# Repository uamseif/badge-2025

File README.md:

# 🛠️ C1b3rtr4cks Badge 2025

Este repositorio contiene el diseño y firmware de la **badge oficial del evento de ciberseguridad [Cibertracks](https://www.c1b3rtr4cks.es/)**. Este badge está compuesta por **tres placas PCB** ensambladas como un **sandwich**, cada una diseñada en **KiCad**. Además de su función identificativa, su forma permite utilizarla como **portatarjetas físico** para credenciales o tarjetas del evento.

---

## 🧭 Descripción del Proyecto

- 🔧 **Diseño multicapa:** 3 placas PCB ensambladas en forma de sandwich.
- 🎨 **Diseño personalizado:** Adaptada para representar visualmente la identidad del evento.
- 💾 **Firmware en C:** Corre en un **CH32V003**, un microcontrolador RISC-V.
- 🪪 **Funcionalidad dual:** Badge electrónica + portatarjetas físico.

---

## 🧩 Hardware

La placa está diseñada en tres capas, cada una como un proyecto independiente en **KiCad**:

- **badge2025**: Capa frontal. Incluye LEDs, botones y detalles gráficos del evento.
- **middle_frame**: Elemento mecánico que actua como separador y de retenedor de tarjetas.
- **front_frame**: Capa frontal que extiende el diseño de la placa principal.

Estas capas se ensamblan de forma compacta, resultando en una badge robusta y funcional, apta para colgar con lanyard o sujetar una tarjeta del evento.

---

## 💻 Firmware

El firmware está ubicado en `software` y está desarrollado en **C** usando **PlatformIO**.

Se trata de una serie de minijuegos a los que se puede jugar con otra persona juntando dos placas. 

### 📦 Requisitos

- [PlatformIO](https://platformio.org/)
- Programador compatible con CH32V003 (ej. WCH-LinkE, USB-UART + BOOT0)

## ▶️ ¿Cómo usar la placa?

En la siguiente [página](HOW-TO-USE.md) encontramos instrucciones de como usar la placa y jugar con ella.

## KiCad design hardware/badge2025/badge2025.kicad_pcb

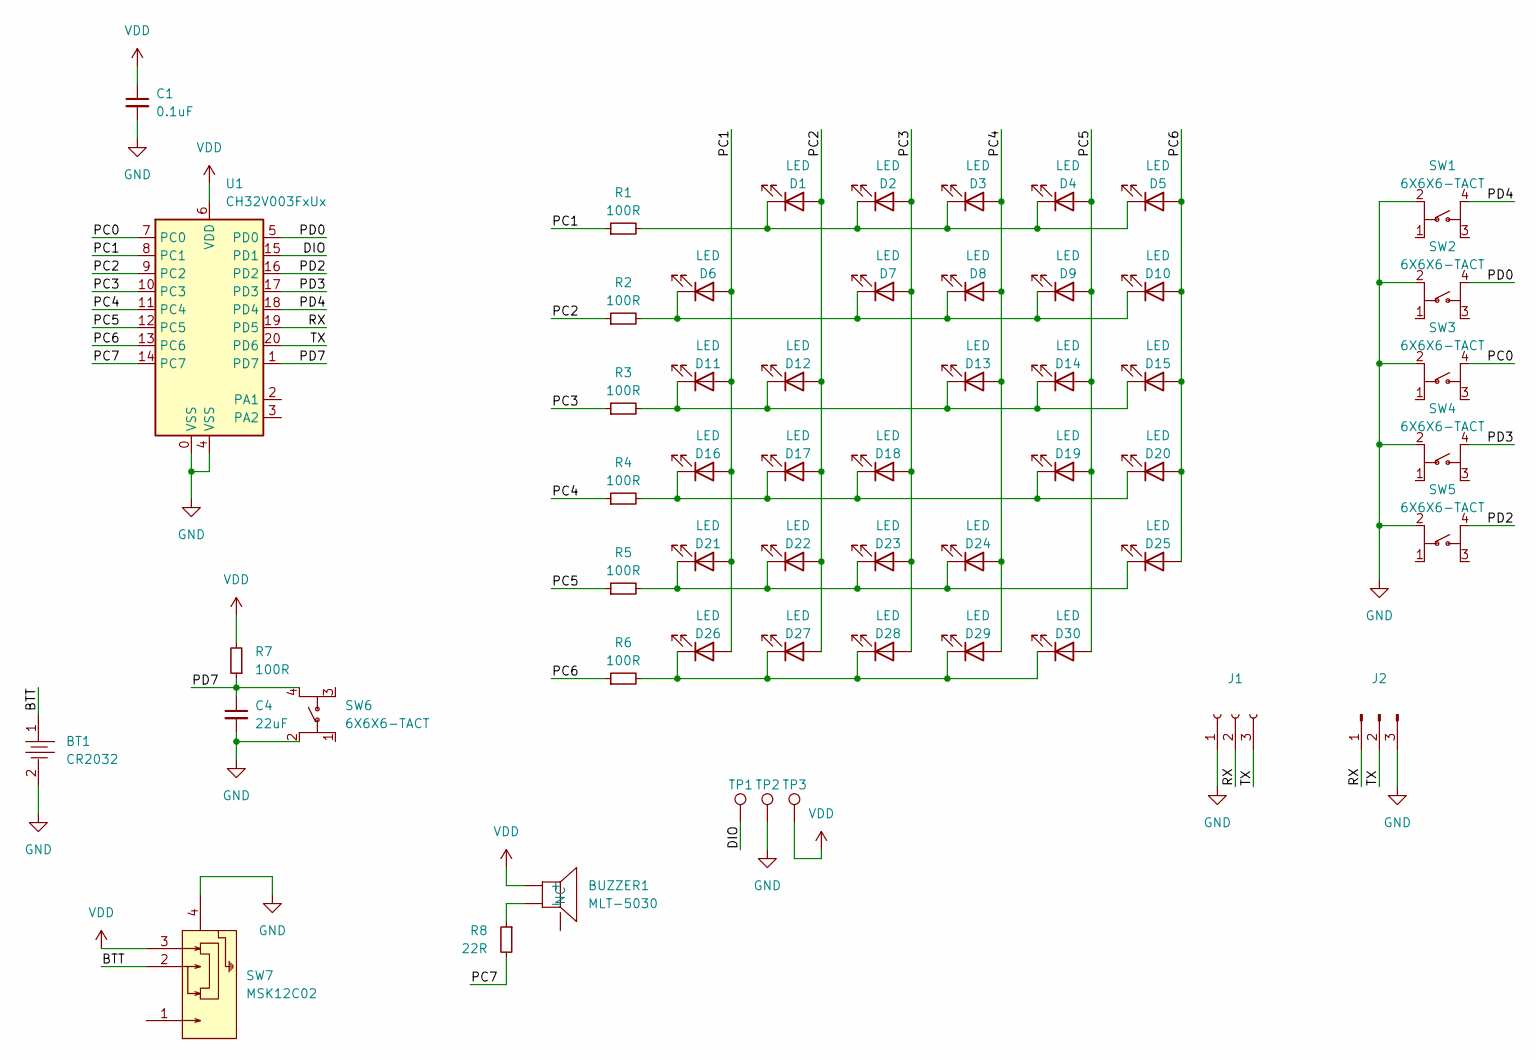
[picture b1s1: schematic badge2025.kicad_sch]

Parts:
BT1: CR2032; BAT-SMD_MY-2032-08
BUZZER1: MLT-5030; BUZ-SMD_3P-L5.2-W5.2-P3.50-BR
C1: 0.1uF; C_0805_2012Metric
C4: 22uF; C_0805_2012Metric
D1, D2, D3, D4, D5, D6, D7, D8, D9, D10, D11, D12, D13, D14, D15, D16, D17, D18, D19, D20, D21, D22, D23, D24, D25, D26, D27, D28, D29, D30: LED; LED_0805_2012Metric
J1: Conn_01x03_Socket; HDR-SMD_3P-P2.54-H-M
J2: Conn_01x03_Pin; HDR-SMD_3P-P2.54-H-F-L11.5
R1, R2, R3, R4, R5, R6, R7: 100R; R_0805_2012Metric
R8: 22R; R_0805_2012Metric
SW1, SW2, SW3, SW4, SW5, SW6: 6X6X6-TACT; SW-SMD_4P-L6.0-W6.0-P4.50-LS9.2
SW7: MSK12C02; SW-TH_MSK12C02
TP1, TP2, TP3: TestPoint; TestPoint_Pad_D1.5mm
U1: CH32V003FxUx; QFN-20-1EP_3x3mm_P0.4mm_EP1.65x1.65mm

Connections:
/BTT: BT1.1, SW7.2
/DIO: TP1.1, U1.15 (PD1)
/PC0: SW3.4 (D), U1.7 (PC0)
/PC1: D6.2 (A), D11.2 (A), D16.2 (A), D21.2 (A), D26.2 (A), R1.1, U1.8 (PC1)
/PC2: D1.2 (A), D12.2 (A), D17.2 (A), D22.2 (A), D27.2 (A), R2.1, U1.9 (PC2)
/PC3: D2.2 (A), D7.2 (A), D18.2 (A), D23.2 (A), D28.2 (A), R3.1, U1.10 (PC3)
/PC4: D3.2 (A), D8.2 (A), D13.2 (A), D24.2 (A), D29.2 (A), R4.1, U1.11 (PC4)
/PC5: D4.2 (A), D9.2 (A), D14.2 (A), D19.2 (A), D30.2 (A), R5.1, U1.12 (PC5)
/PC6: D5.2 (A), D10.2 (A), D15.2 (A), D20.2 (A), D25.2 (A), R6.1, U1.13 (PC6)
/PC7: R8.2, U1.14 (PC7)
/PD0: SW2.4 (D), U1.5 (PD0)
/PD2: SW5.4 (D), U1.16 (PD2)
/PD3: SW4.4 (D), U1.17 (PD3)
/PD4: SW1.4 (D), U1.18 (PD4)
/PD7: C4.1, R7.1, SW6.4 (D), U1.1 (PD7)
/RX: J1.2, J2.1, U1.19 (PD5)
/TX: J1.3, J2.2, U1.20 (PD6)
/XI: U1.2 (PA1)
/XO: U1.3 (PA2)
GND: BT1.2, C1.2, C4.2, J1.1, J2.3, SW1.2 (B), SW2.2 (B), SW3.2 (B), SW4.2 (B), SW5.2 (B), SW6.2 (B), SW7.4, TP2.1, U1.0 (VSS), U1.4 (VSS)
unnamed: BUZZER1.3 (-), R8.1
unnamed: D1.1 (K), D2.1 (K), D3.1 (K), D4.1 (K), D5.1 (K), R1.2
unnamed: D6.1 (K), D7.1 (K), D8.1 (K), D9.1 (K), D10.1 (K), R2.2
unnamed: D11.1 (K), D12.1 (K), D13.1 (K), D14.1 (K), D15.1 (K), R3.2
unnamed: D16.1 (K), D17.1 (K), D18.1 (K), D19.1 (K), D20.1 (K), R4.2
unnamed: D21.1 (K), D22.1 (K), D23.1 (K), D24.1 (K), D25.1 (K), R5.2
unnamed: D26.1 (K), D27.1 (K), D28.1 (K), D29.1 (K), D30.1 (K), R6.2
VDD: BUZZER1.2 (+), C1.1, R7.2, SW7.3, TP3.1, U1.6 (VDD)

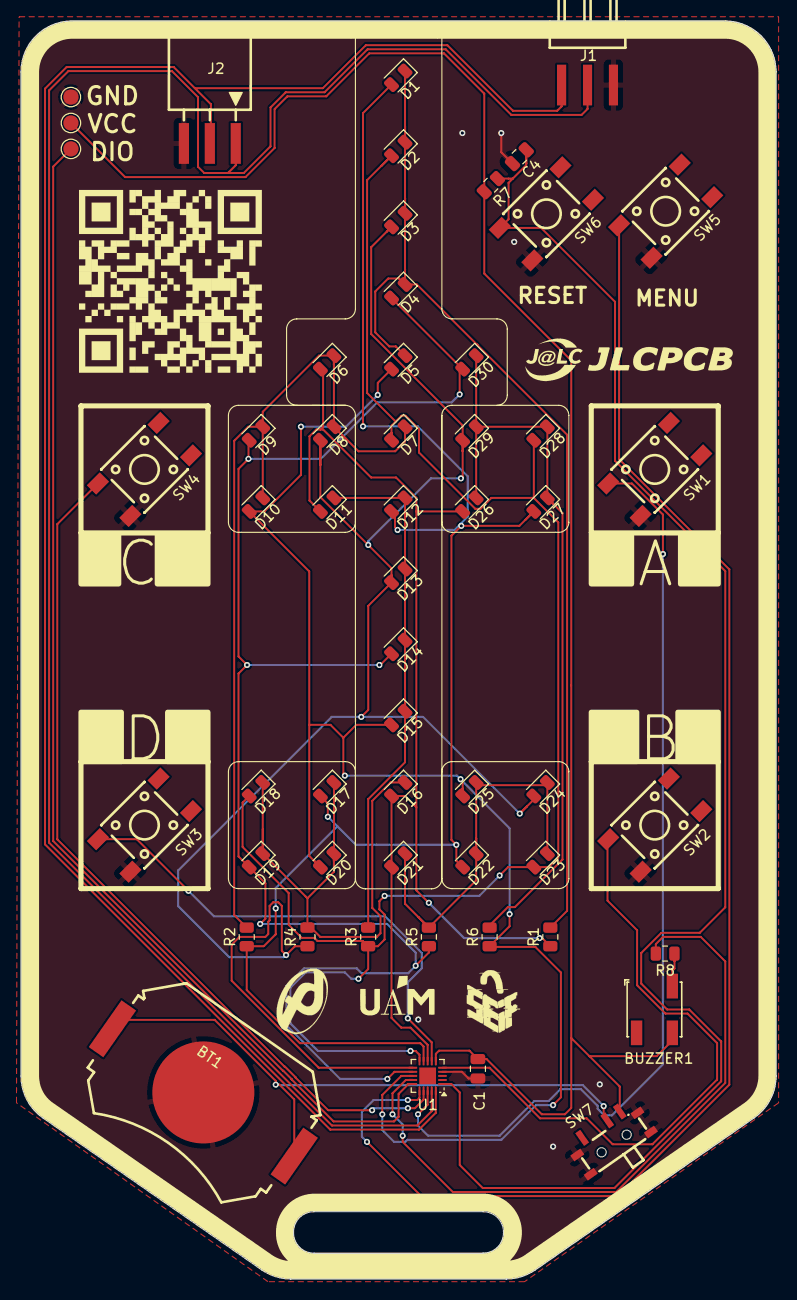
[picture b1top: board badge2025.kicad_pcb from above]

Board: 2 copper layers, 74.0 x 123.3 mm, 55 parts (0 on the bottom side), 26 nets.

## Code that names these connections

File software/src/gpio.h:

#pragma once

#include "ch32v003_GPIO_branchless.h"
#include "definitions.h"
#include "lib_uart.h"

#define MS_TO_TICKS(ms) ((ms) * 48)

#define LED_MATRIX_NUM_PINS     6
#define LED_MATRIX_SIZE     (LED_MATRIX_NUM_PINS * (LED_MATRIX_NUM_PINS - 1))
#define BUTTON_COUNT            5

#define PIN_BEEP             PC7

#define PIN_BUTTON_A         PD4
#define PIN_BUTTON_B         PD0
#define PIN_BUTTON_C         PD3
#define PIN_BUTTON_D         PC0
#define PIN_BUTTON_MENU      PD2

#define BUTTON_A             0
#define BUTTON_B             1
#define BUTTON_C             2
#define BUTTON_D             3
#define BUTTON_MENU          4
#define DEBOUNCE_DELAY_MS    2000

#define UART_BUFFER_SIZE 32
uint8_t uart_buffer[UART_BUFFER_SIZE];
size_t uart_bytes_read;

static uint32_t last_millis = 0;

uint8_t leds_buffer[LED_MATRIX_SIZE];
#define BUZZER_BUFFER_SIZE 10
Sound sound_buffer[BUZZER_BUFFER_SIZE];
uint8_t buzzer_head = 0, buzzer_tail = 0, buzzer_count = 0, buzzer_state = 0;
static uint32_t buzzer_millis = 0;

Button buttons[BUTTON_COUNT];

extern volatile uint32_t systick_millis;

int led_positions[LED_MATRIX_SIZE][2] = {
    {PC1, PC2}, // LED 1
    {PC1, PC3}, // LED 2
    {PC1, PC4}, // LED 3
    {PC1, PC5}, // LED 4
    {PC1, PC6}, // LED 5

    {PC2, PC1}, // LED 6
    {PC2, PC3}, // LED 7
    {PC2, PC4}, // LED 8
    {PC2, PC5}, // LED 9
    {PC2, PC6}, // LED 10

    {PC3, PC1}, // LED 11
    {PC3, PC2}, // LED 12
    {PC3, PC4}, // LED 13
    {PC3, PC5}, // LED 14
    {PC3, PC6}, // LED 15

    {PC4, PC1}, // LED 16
    {PC4, PC2}, // LED 17
    {PC4, PC3}, // LED 18
    {PC4, PC5}, // LED 19
    {PC4, PC6}, // LED 20

    {PC5, PC1}, // LED 21
    {PC5, PC2}, // LED 22
    {PC5, PC3}, // LED 23
    {PC5, PC4}, // LED 24
    {PC5, PC6}, // LED 25

    {PC6, PC1}, // LED 26
    {PC6, PC2}, // LED 27
    {PC6, PC3}, // LED 28
    {PC6, PC4}, // LED 29
    {PC6, PC5}, // LED 30
};

static inline void led_matrix_init()
{
    GPIO_port_enable(GPIO_port_C);
}

static inline void led_matrix_run()
{
    static int ledIndex = 0;


    GPIO_pinMode(led_positions[ledIndex][0], GPIO_pinMode_I_floating, GPIO_Speed_10MHz);
    GPIO_pinMode(led_positions[ledIndex][1], GPIO_pinMode_I_floating, GPIO_Speed_10MHz);

    ledIndex++;

    if (ledIndex >= LED_MATRIX_SIZE) {
        ledIndex = 0;
    }

    const uint8_t led = leds_buffer[ledIndex];

    if (led) {
        GPIO_pinMode(led_positions[ledIndex][0], GPIO_pinMode_O_pushPull, GPIO_Speed_10MHz);
        GPIO_pinMode(led_positions[ledIndex][1], GPIO_pinMode_O_pushPull, GPIO_Speed_10MHz);

        GPIO_digitalWrite(led_positions[ledIndex][0], low);
        GPIO_digitalWrite(led_positions[ledIndex][1], high);
    }

}

static inline void clear_leds() {
    for (int i = 0; i < LED_MATRIX_SIZE; i++) {
        leds_buffer[i] = 0;
    }
}

static inline void buzzer_init() {
    GPIO_port_enable(GPIO_port_C);

}

static inline void add_sound(uint32_t frequency, uint32_t duration) {
    if (buzzer_count < BUZZER_BUFFER_SIZE) {
        sound_buffer[buzzer_tail].frequency = frequency;
        sound_buffer[buzzer_tail].duration = duration;
        buzzer_tail = (buzzer_tail + 1) % BUZZER_BUFFER_SIZE;
        buzzer_count++;
    } else {
#ifdef DEBUG
        printf("Buffer lleno, no se puede agregar sonido.\n");
#endif
    }
}


static inline void buzzer_run() {
    const uint32_t currentMillis = systick_millis;
    if (buzzer_count > 0) {
        if (currentMillis - buzzer_millis >= sound_buffer[buzzer_head].frequency) {
            buzzer_state = buzzer_state  == 0 ? 1 : 0;
            buzzer_millis = currentMillis;
            if (buzzer_state == 1) {
                GPIO_pinMode(PIN_BEEP, GPIO_pinMode_O_pushPull, GPIO_Speed_10MHz);
            } else {
                GPIO_pinMode(PIN_BEEP, GPIO_pinMode_I_floating, GPIO_Speed_10MHz);
            }
        }
        sound_buffer[buzzer_head].duration--;

        if (sound_buffer[buzzer_head].duration <= 0) {
            buzzer_head = (buzzer_head + 1) % BUZZER_BUFFER_SIZE;
            buzzer_count--;
        }
    }
}

static inline int button_is_pressed(const uint8_t btn) {
    Button *button = &buttons[btn];
    const int currentState = GPIO_digitalRead(button->pin) == 1;

    uint32_t now = systick_millis;

    if (currentState != button->lastState) {
        button->lastDebounceTime = now;
    }

    if ((now - button->lastDebounceTime) > DEBOUNCE_DELAY_MS) {
        if (currentState != button->debouncedState) {
            button->debouncedState = currentState;

            if (button->debouncedState == 0) {
                button->lastState = currentState;
                return 1;
            }
        }
    }

    button->lastState = currentState;
    return 0;
}

static inline void buttons_init() {
    GPIO_port_enable(GPIO_port_D);
    GPIO_port_enable(GPIO_port_C);

    buttons[BUTTON_A].pin = PIN_BUTTON_A;
    buttons[BUTTON_B].pin = PIN_BUTTON_B;
    buttons[BUTTON_C].pin = PIN_BUTTON_C;
    buttons[BUTTON_D].pin = PIN_BUTTON_D;
    buttons[BUTTON_MENU].pin = PIN_BUTTON_MENU;

    for (int i = 0; i < BUTTON_COUNT; i++) {
        GPIO_pinMode(buttons[i].pin, GPIO_pinMode_I_pullUp, GPIO_Speed_10MHz);
    }

}


static inline void gpio_uart_init() {
    // Create a UART Configuration
    uart_config_t uart_conf = {
        .baudrate    = UART_BAUD_9600,
        .wordlength  = UART_WORDLENGTH_8,
        .parity      = UART_PARITY_NONE,
        .stopbits    = UART_STOPBITS_ONE,
        .flowctrl    = UART_FLOWCTRL_NONE,
    };

    uart_err_t err_state;

    // Initialise the UART
    err_state = uart_init(uart_buffer, UART_BUFFER_SIZE, &uart_conf );
    if(err_state != UART_OK)
    {
#ifdef DEBUG
        printf("Failed to Initialise the UART\n");
#endif
    }
}

static inline void gpio_uart_read() {
    uart_bytes_read = uart_read(uart_buffer, UART_BUFFER_SIZE);
}

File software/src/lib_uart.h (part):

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
#define RX_RING_BUFFER_OVERWRITE

NOTE: UART_ALTERNATE_1 will disable SWIO (PD1)

Pinout        TX        RX        CTS        RTS
Default       PD5       PD6       PD3        PC2
Alternate 1   PD0       PD1       PC3        PC2
Alternate 2   PD6       PD5       PC6        PC7
Alternate 3   PC0       PC1       PC6        PC7

#define UART_PINOUT_DEFAULT
#define UART_PINOUT_ALTERNATE_1
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
// Default Pinout
// TX        RX        CTS        RTS
// PD5       PD6       PD3        PC2
#ifdef UART_PINOUT_DEFAULT
	#define UART_AFIO_MASK       ((uint32_t)0x00000000)
	//
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#endif

// Alternate Pinout 1
// This will Disable SWIO (PD1)
// TX        RX        CTS        RTS
// PD0       PD1       PC3        PC2
#ifdef UART_PINOUT_ALTERNATE_1
	#define UART_AFIO_MASK       ((uint32_t)0x04000004)
	//
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
// Alternate Pinout 2
// TX        RX        CTS        RTS
// PD6       PD5       PC6        PC7
#ifdef UART_PINOUT_ALTERNATE_2
	#define UART_AFIO_MASK       ((uint32_t)0x00200000)
	//
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
// Alternate Pinout 3
// TX        RX        CTS        RTS
// PC0       PC1       PC6        PC7
#ifdef UART_PINOUT_ALTERNATE_3
	#define UART_AFIO_MASK       ((uint32_t)0x00200004)
	//
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

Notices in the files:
software/src/lib_uart.h:
Released under the MIT Licence
Copyright ADBeta (c) 2024
